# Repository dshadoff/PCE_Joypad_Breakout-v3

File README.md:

# PCE_Joypad_Breakout-v3

This project was made in the EAGLE PC Board design packagei (free version),
to assist in the development and experimentation of new joypad devices for
the PC Engine videogame system.

Features include:
- a prototype-style area for mounting projects
- 3.3V regulator and level-shift logic for alternate inputs
- 5V inputs for pass-through and switched operation, as a Memory Base 128
would do

This project also includes the Gerber files, which you can download and
send to your favorite PC Board fabrication company, to make some for
yourself.

# Important:

Do not place a heavy load on this device,  especially if your console has
been modified in any way, as the power supply may already have a higher load
on it than intended.  This device draws power from the PC Engine's joypad
port, which has limited power available. Overloading this circuit may cause
irreparable damage to the PC Engine unit.  I cannot be held responsible for
damage caused for this (or any other) reason.

You should only use this board if you:
a) Understand what it does, and know the impacts of using it with your
protoype, and
b) Understand and accept the risks of using it.

Loads required by average, licensed devices (for reference):
Joypad: approx. 1 mA
PCE Mouse: approx. 6 mA
Memory Base 128: approx 15 mA

# Notes:

The header at the top of the board is the same pinout as that on the inside
of a PC Engine joypad (where the cable meets the board). If you can find a
compatible replacement cable (such as at a website like Console5.com), such
a cable should work... however, be careful about orientation: the "GND"
wire at the end of the pin header shouls connect with the round metal
portion of the mini-DIN plug.

The header immediately adjacent is 5V-logic outputs, feeding to the PCE.

The header adjacent to the mini-DIN jack is for measuring the data back
from the connected peripheral (note: depending on the swithcing logic,
this may or may not be the data fed back to the PCE).

The jumper at the bottom-right of the board can be placed in one of
three positions, to determine which input is sent to the PC Engine:
- bottom position (center bridged with bottom): always send input from
the 5V joypad connector
- top position (center bridged with top): always send input from the
3.3V connector on the right (prototype)
- middle position (center-left bridged with center-right): switch based
on 3.3V value from the pin at the very bottom of the right-hand header
(separated slightly from the main group of pins).
OR, if you would like to drive the selector from 5V logic, do not jumper,
and attach the 5V signal to the center-left pin.
LOW = PC Engine mini-DIN input
HIGH = 3.3V mini-DIN input

The two jumpers within the 3.3V bock (at D1 and D3) bring those inputs
to ground, and are useful if emulating the MB128 peripheral.

# Errata:

This board lacks pullup resistors on the D0-D3 lines on both the
5V inputs and the 3.3V inputs.  This could be a problem if that input
is 'active' while on input is connected - random data will appear for
those bits.  (This will eb fixed in a subsequent version).

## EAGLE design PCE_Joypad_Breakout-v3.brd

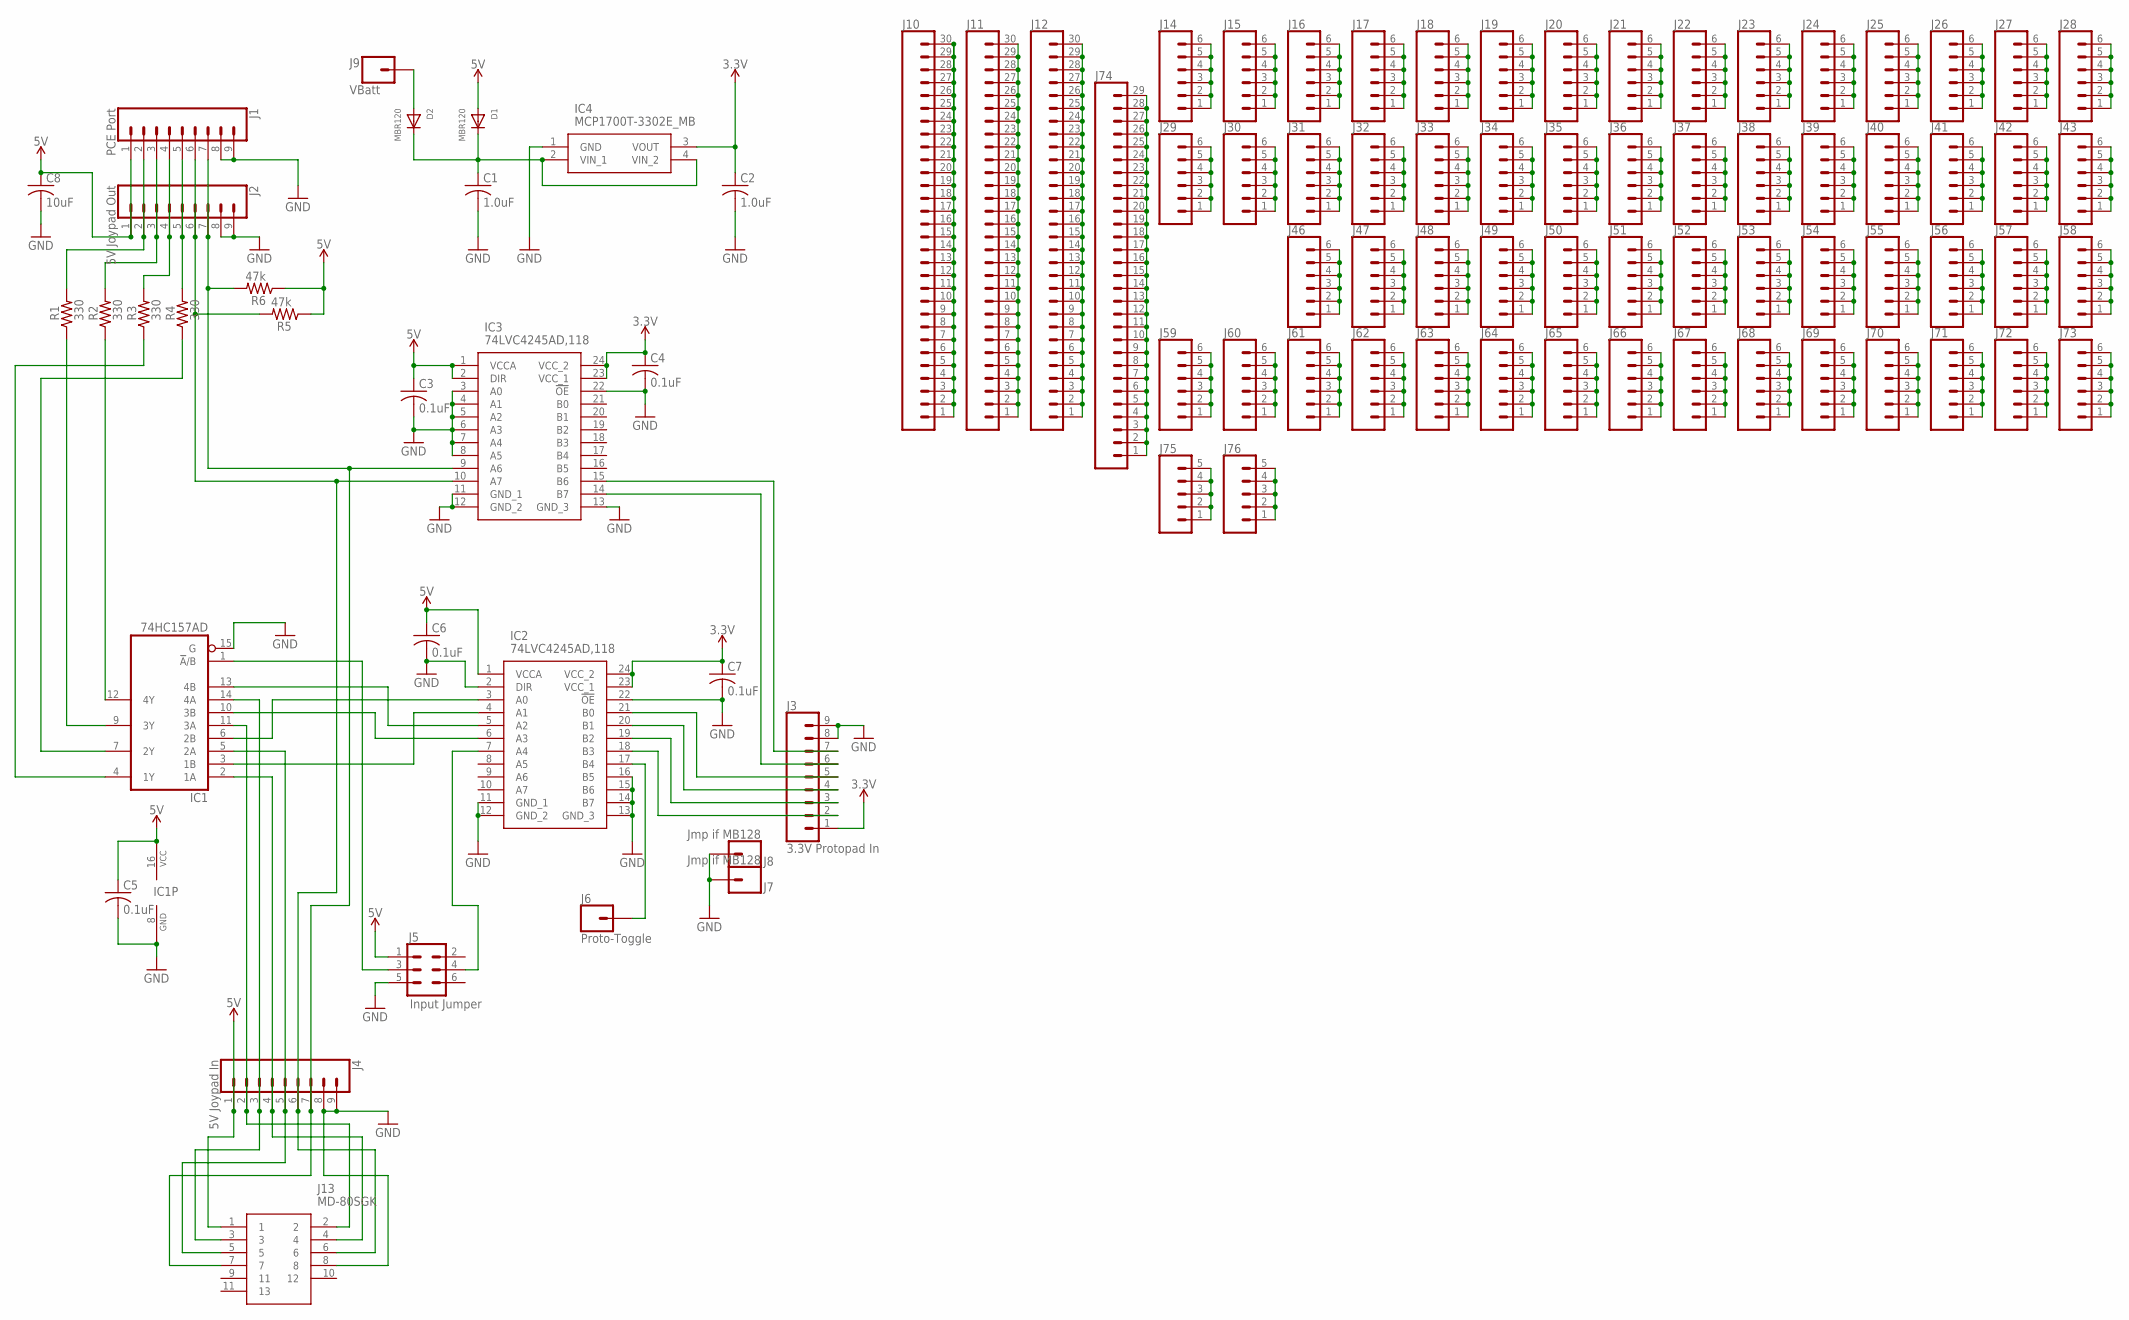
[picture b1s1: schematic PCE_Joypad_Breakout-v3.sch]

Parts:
C1, C2: 1.0uF; C0805
C3, C4, C5, C6, C7: 0.1uF; C0805
C8: 10uF; C0805
D1, D2: MBR120; SOD-123
IC1: 74HC157AD; SO16
IC2, IC3: 74LVC4245AD,118; SOIC127P1032X265-24N
IC4: MCP1700T-3302E_MB; MCP1700T-3302E/MB
J1: PCE Port; 1X09
J2: 5V Joypad Out; 1X09
J3: 3.3V Protopad In; 1X09
J4: 5V Joypad In; 1X09
J5: Input Jumper; 2X3
J6: Proto-Toggle; 1X01
J7, J8: Jmp if MB128; 1X01
J9: VBatt; 1X01
J10, J11, J12: CONN_30NO_SILK; 1X30_NO_SILK
J13: MD-80SGK; MD80SGK
J14, J15, J16, J17, J18, J19, J20, J21, J22, J23, J24, J25, J26, J27, J28, J29, J30, J31, J32, J33, J34, J35, J36, J37, J38, J39, J40, J41, J42, J43, J46, J47, J48, J49, J50, J51, J52, J53, J54, J55, J56, J57, J58, J59, J60, J61, J62, J63, J64, J65, J66, J67, J68, J69, J70, J71, J72, J73: CONN_06NO_SILK_FEMALE_PTH; 1X06_NO_SILK
J74: CONN_29NO_SILK; 1X29_NO_SILK
J75, J76: CONN_05NO_SILK; 1X05_NO_SILK
R1, R2, R3, R4: 330; R0805
R5, R6: 47k; R0805

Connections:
3.3V: C2.1, C4.1, C7.1, IC2.23 (VCC_1), IC2.24 (VCC_2), IC3.23 (VCC_1), IC3.24 (VCC_2), IC4.3 (VOUT), J3.1
5V: C3.1, C5.1, C6.1, C8.1, D1.A, IC1.16 (VCC), IC2.1 (VCCA), IC3.1 (VCCA), IC3.2 (DIR), J1.1, J2.1, J4.1, J5.1, J13.1, R5.1, R6.1
GND: C1.2, C2.2, C3.2, C4.2, C5.2, C6.2, C7.2, C8.2, IC1.8 (GND), IC1.15 (G), IC2.2 (DIR), IC2.11 (GND_1), IC2.12 (GND_2), IC2.13 (GND_3), IC2.14 (B7), IC2.15 (B6), IC2.16 (B5), IC2.22 (!OE), IC3.3 (A0), IC3.4 (A1), IC3.5 (A2), IC3.6 (A3), IC3.7 (A4), IC3.8 (A5), IC3.11 (GND_1), IC3.12 (GND_2), IC3.13 (GND_3), IC3.22 (!OE), IC4.1 (GND), J1.8, J1.9, J2.8, J2.9, J3.8, J3.9, J4.8, J4.9, J5.5, J7.1, J8.1, J13.8
unnamed: J1.4, J2.4, R3.2
unnamed: C1.1, D1.C, D2.C, IC4.2 (VIN_1), IC4.4 (VIN_2)
unnamed: J1.2, J2.2, R1.2
unnamed: J1.3, J2.3, R2.2
unnamed: IC1.11 (3A), J4.2, J13.2
unnamed: J1.5, J2.5, R4.2
unnamed: IC1.9 (3Y), R1.1
unnamed: IC3.9 (A6), J1.7, J2.7, J4.7, J13.7, R6.2
unnamed: IC1.14 (4A), J4.3, J13.3
unnamed: IC1.2 (1A), J4.4, J13.4
unnamed: IC1.5 (2A), J4.5, J13.5
unnamed: IC3.14 (B7), J3.6
unnamed: IC3.15 (B6), J3.7
unnamed: IC1.6 (2B), IC2.3 (A0)
unnamed: IC1.13 (4B), IC2.5 (A2)
unnamed: IC1.10 (3B), IC2.6 (A3)
unnamed: IC3.10 (A7), J1.6, J2.6, J4.6, J13.6, R5.2
unnamed: IC1.3 (1B), IC2.4 (A1)
unnamed: IC1.4 (1Y), R3.1
unnamed: IC1.7 (2Y), R4.1
unnamed: IC2.21 (B0), J3.5
unnamed: IC2.20 (B1), J3.4
unnamed: IC2.19 (B2), J3.3
unnamed: IC1.1 (!A!/B), J5.3
unnamed: IC2.7 (A4), J5.4
unnamed: D2.A, J9.1
unnamed: IC2.17 (B4), J6.1
unnamed: J10.1, J10.2, J10.3, J10.4, J10.5, J10.6, J10.7, J10.8, J10.9, J10.10, J10.11, J10.12, J10.13, J10.14, J10.15, J10.16, J10.17, J10.18, J10.19, J10.20, J10.21, J10.22, J10.23, J10.24, J10.25, J10.26, J10.27, J10.28, J10.29, J10.30
unnamed: J11.1, J11.2, J11.3, J11.4, J11.5, J11.6, J11.7, J11.8, J11.9, J11.10, J11.11, J11.12, J11.13, J11.14, J11.15, J11.16, J11.17, J11.18, J11.19, J11.20, J11.21, J11.22, J11.23, J11.24, J11.25, J11.26, J11.27, J11.28, J11.29, J11.30
unnamed: J12.1, J12.2, J12.3, J12.4, J12.5, J12.6, J12.7, J12.8, J12.9, J12.10, J12.11, J12.12, J12.13, J12.14, J12.15, J12.16, J12.17, J12.18, J12.19, J12.20, J12.21, J12.22, J12.23, J12.24, J12.25, J12.26, J12.27, J12.28, J12.29, J12.30
unnamed: IC1.12 (4Y), R2.1
unnamed: J14.1, J14.2, J14.3, J14.4, J14.5, J14.6
unnamed: J29.1, J29.2, J29.3, J29.4, J29.5, J29.6
unnamed: J15.1, J15.2, J15.3, J15.4, J15.5, J15.6
unnamed: J30.1, J30.2, J30.3, J30.4, J30.5, J30.6
unnamed: J31.1, J31.2, J31.3, J31.4, J31.5, J31.6
unnamed: J16.1, J16.2, J16.3, J16.4, J16.5, J16.6
unnamed: J17.1, J17.2, J17.3, J17.4, J17.5, J17.6
unnamed: J32.1, J32.2, J32.3, J32.4, J32.5, J32.6
unnamed: J33.1, J33.2, J33.3, J33.4, J33.5, J33.6
unnamed: J18.1, J18.2, J18.3, J18.4, J18.5, J18.6
unnamed: J19.1, J19.2, J19.3, J19.4, J19.5, J19.6
unnamed: J20.1, J20.2, J20.3, J20.4, J20.5, J20.6
unnamed: J21.1, J21.2, J21.3, J21.4, J21.5, J21.6
unnamed: J22.1, J22.2, J22.3, J22.4, J22.5, J22.6
unnamed: J23.1, J23.2, J23.3, J23.4, J23.5, J23.6
unnamed: J24.1, J24.2, J24.3, J24.4, J24.5, J24.6
unnamed: J25.1, J25.2, J25.3, J25.4, J25.5, J25.6
unnamed: J26.1, J26.2, J26.3, J26.4, J26.5, J26.6
unnamed: J27.1, J27.2, J27.3, J27.4, J27.5, J27.6
unnamed: J28.1, J28.2, J28.3, J28.4, J28.5, J28.6
unnamed: J34.1, J34.2, J34.3, J34.4, J34.5, J34.6
unnamed: J35.1, J35.2, J35.3, J35.4, J35.5, J35.6
unnamed: J36.1, J36.2, J36.3, J36.4, J36.5, J36.6
unnamed: J37.1, J37.2, J37.3, J37.4, J37.5, J37.6
unnamed: J38.1, J38.2, J38.3, J38.4, J38.5, J38.6
unnamed: J39.1, J39.2, J39.3, J39.4, J39.5, J39.6
unnamed: J40.1, J40.2, J40.3, J40.4, J40.5, J40.6
unnamed: J41.1, J41.2, J41.3, J41.4, J41.5, J41.6
unnamed: J42.1, J42.2, J42.3, J42.4, J42.5, J42.6
unnamed: J43.1, J43.2, J43.3, J43.4, J43.5, J43.6
unnamed: J75.1, J75.2, J75.3, J75.4, J75.5
unnamed: J76.1, J76.2, J76.3, J76.4, J76.5
unnamed: J46.1, J46.2, J46.3, J46.4, J46.5, J46.6
unnamed: J47.1, J47.2, J47.3, J47.4, J47.5, J47.6
unnamed: J48.1, J48.2, J48.3, J48.4, J48.5, J48.6
unnamed: J49.1, J49.2, J49.3, J49.4, J49.5, J49.6
unnamed: J50.1, J50.2, J50.3, J50.4, J50.5, J50.6
unnamed: J51.1, J51.2, J51.3, J51.4, J51.5, J51.6
unnamed: J52.1, J52.2, J52.3, J52.4, J52.5, J52.6
unnamed: J53.1, J53.2, J53.3, J53.4, J53.5, J53.6
unnamed: J54.1, J54.2, J54.3, J54.4, J54.5, J54.6
unnamed: J55.1, J55.2, J55.3, J55.4, J55.5, J55.6
unnamed: J56.1, J56.2, J56.3, J56.4, J56.5, J56.6
unnamed: J57.1, J57.2, J57.3, J57.4, J57.5, J57.6
unnamed: J58.1, J58.2, J58.3, J58.4, J58.5, J58.6
unnamed: J59.1, J59.2, J59.3, J59.4, J59.5, J59.6
unnamed: J60.1, J60.2, J60.3, J60.4, J60.5, J60.6
unnamed: J61.1, J61.2, J61.3, J61.4, J61.5, J61.6
unnamed: J62.1, J62.2, J62.3, J62.4, J62.5, J62.6
unnamed: J63.1, J63.2, J63.3, J63.4, J63.5, J63.6
unnamed: J64.1, J64.2, J64.3, J64.4, J64.5, J64.6
unnamed: J65.1, J65.2, J65.3, J65.4, J65.5, J65.6
unnamed: J66.1, J66.2, J66.3, J66.4, J66.5, J66.6
unnamed: J67.1, J67.2, J67.3, J67.4, J67.5, J67.6
unnamed: J68.1, J68.2, J68.3, J68.4, J68.5, J68.6
unnamed: J69.1, J69.2, J69.3, J69.4, J69.5, J69.6
unnamed: J70.1, J70.2, J70.3, J70.4, J70.5, J70.6
unnamed: J71.1, J71.2, J71.3, J71.4, J71.5, J71.6
unnamed: J72.1, J72.2, J72.3, J72.4, J72.5, J72.6
unnamed: J73.1, J73.2, J73.3, J73.4, J73.5, J73.6
unnamed: J74.1, J74.2, J74.3, J74.4, J74.5, J74.6, J74.7, J74.8, J74.9, J74.10, J74.11, J74.12, J74.13, J74.14, J74.15, J74.16, J74.17, J74.18, J74.19, J74.20, J74.21, J74.22, J74.23, J74.24, J74.25, J74.26, J74.27, J74.28, J74.29
unnamed: IC2.18 (B3), J3.2

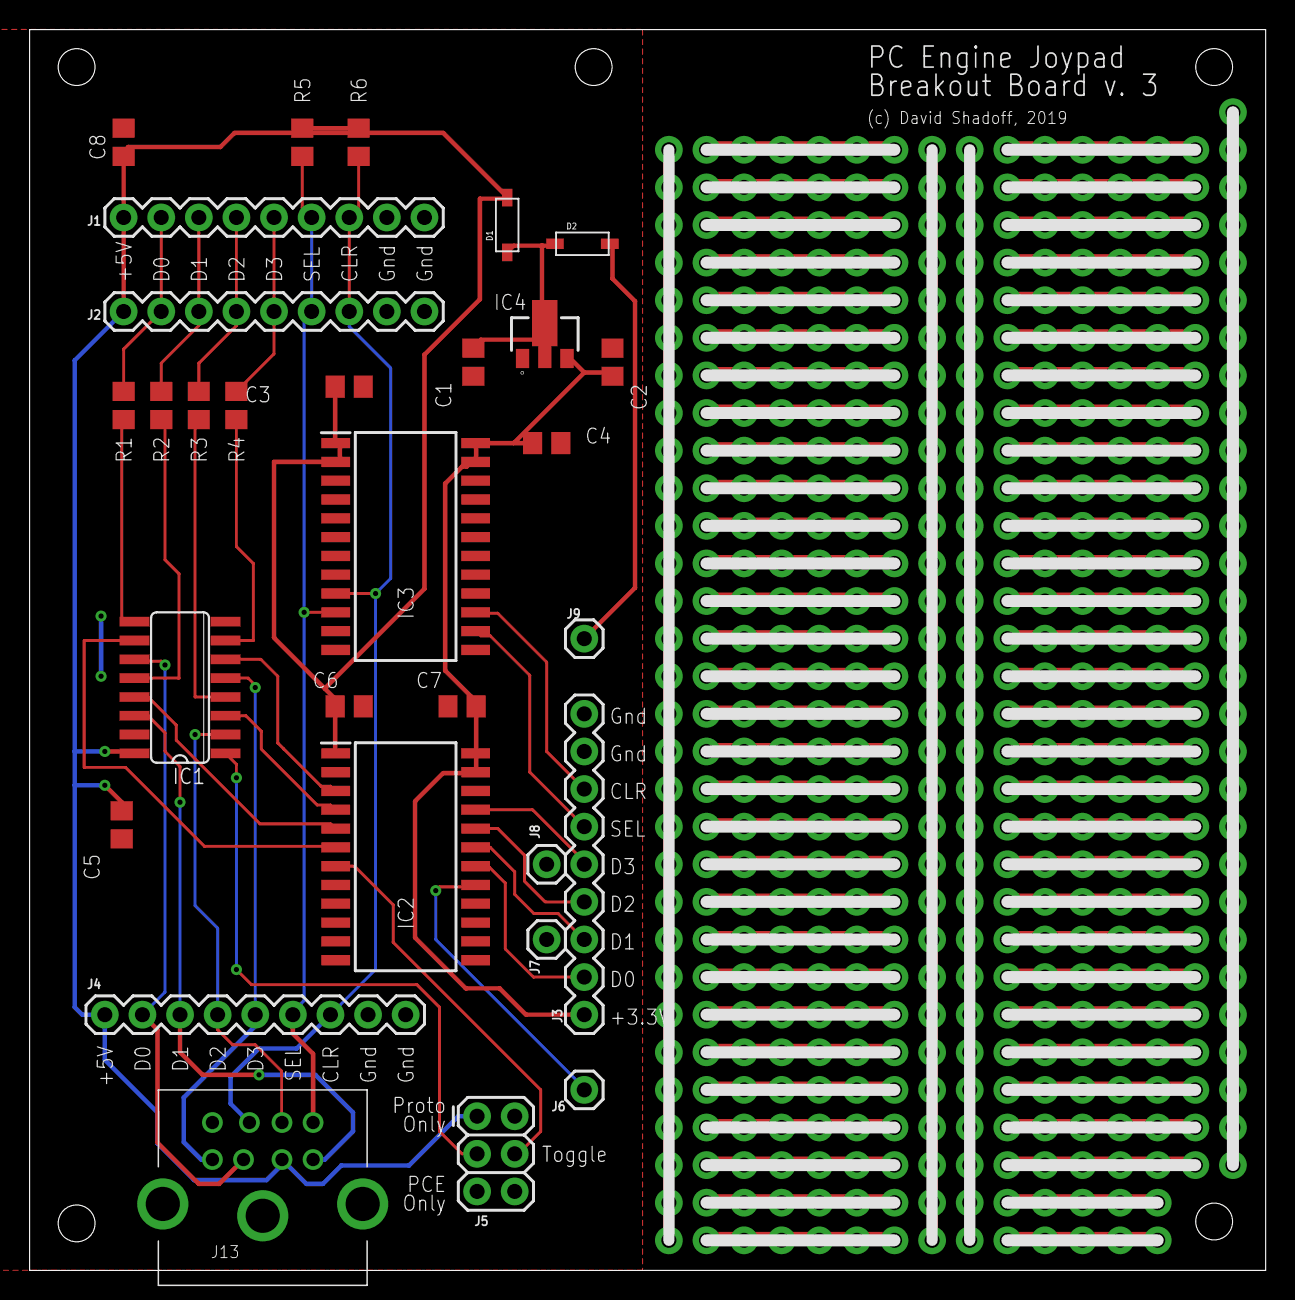
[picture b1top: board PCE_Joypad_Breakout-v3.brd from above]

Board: 2 copper layers, 83.5 x 83.8 mm, 94 parts (0 on the bottom side), 96 nets.

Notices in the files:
parts and their libraries:
SparkFun-Connectors: Licensing: Creative Commons ShareAlike 4.0 International - https://creativecommons.org/licenses/by-sa/4.0
